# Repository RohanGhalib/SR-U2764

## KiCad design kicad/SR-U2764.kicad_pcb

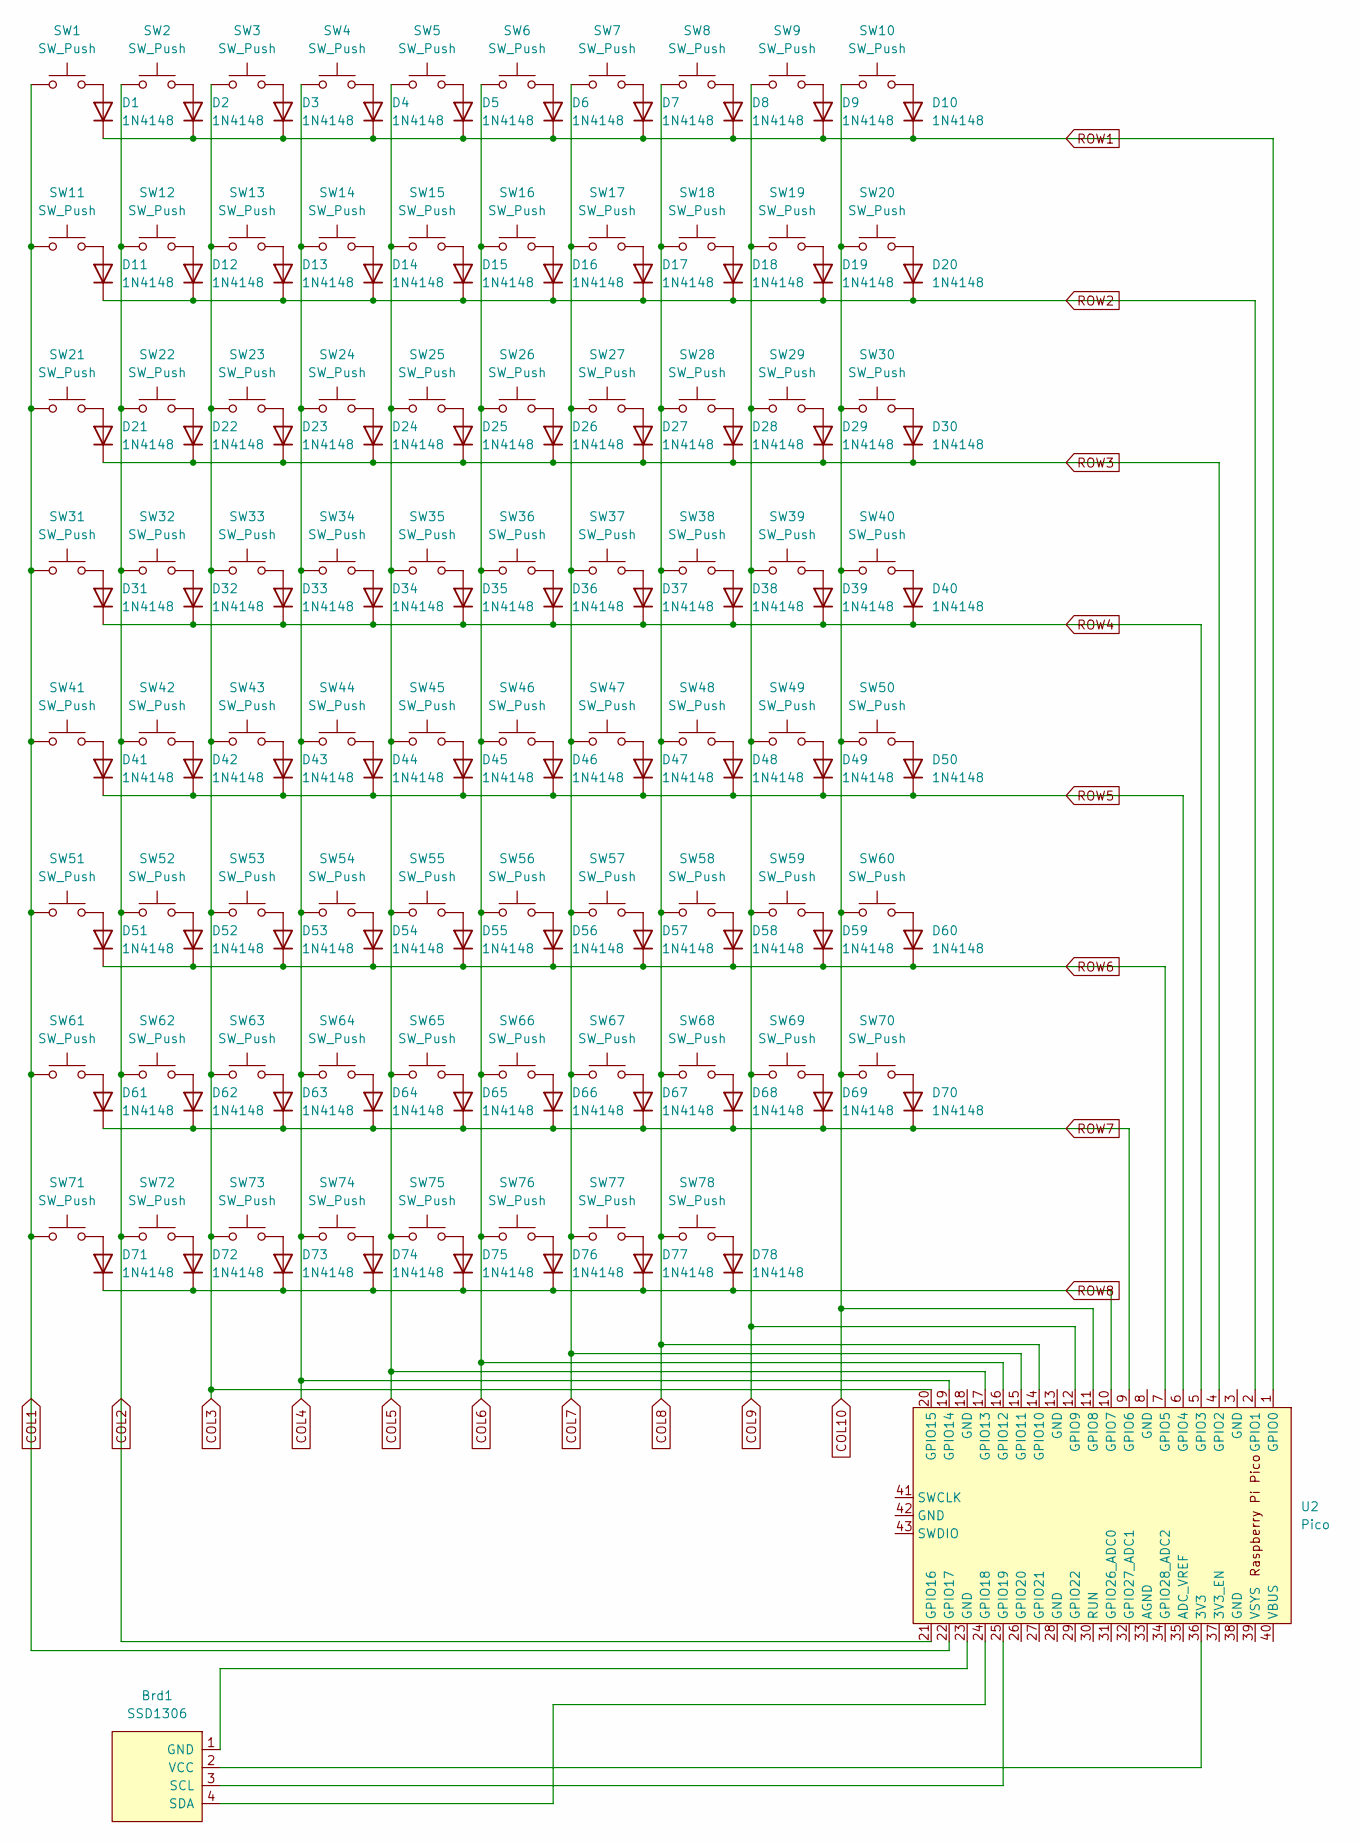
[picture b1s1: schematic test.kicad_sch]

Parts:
Brd1: SSD1306; Adafruit_SSD1306
D1, D2, D3, D4, D5, D6, D7, D8, D9, D10, D11, D12, D13, D14, D15, D16, D17, D18, D19, D20, D21, D22, D23, D24, D25, D26, D27, D28, D29, D30, D31, D32, D33, D34, D35, D36, D37, D38, D39, D40, D41, D42, D43, D44, D45, D46, D47, D48, D49, D50, D51, D52, D53, D54, D55, D56, D57, D58, D59, D60, D61, D62, D63, D64, D65, D66, D67, D68, D69, D70, D71, D72, D73, D74, D75, D76, D77, D78: 1N4148; D_DO-35_SOD27_P7.62mm_Horizontal
SW1, SW2, SW3, SW4, SW5, SW6, SW7, SW8, SW9, SW10, SW11, SW12, SW13, SW14, SW15, SW16, SW17, SW18, SW19, SW20, SW21, SW22, SW23, SW24, SW25, SW26, SW27, SW28, SW29, SW30, SW31, SW32, SW33, SW34, SW35, SW36, SW37, SW38, SW39, SW40, SW41, SW42, SW43, SW44, SW45, SW46, SW47, SW48, SW49, SW50, SW51, SW52, SW53, SW54, SW55, SW56, SW57, SW58, SW59, SW60, SW61, SW62, SW63, SW64, SW65, SW66, SW67, SW68, SW69, SW70, SW71, SW72, SW73, SW74, SW75, SW76, SW77, SW78: SW_Push; SW_Cherry_MX_1.00u_PCB
U2: Pico; RaspberryPi_Pico_Common_THT

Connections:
COL1: SW1.1, SW11.1, SW21.1, SW31.1, SW41.1, SW51.1, SW61.1, SW71.1, U2.22 (GPIO17)
COL2: SW2.1, SW12.1, SW22.1, SW32.1, SW42.1, SW52.1, SW62.1, SW72.1, U2.21 (GPIO16)
COL3: SW3.1, SW13.1, SW23.1, SW33.1, SW43.1, SW53.1, SW63.1, SW73.1, U2.20 (GPIO15)
COL4: SW4.1, SW14.1, SW24.1, SW34.1, SW44.1, SW54.1, SW64.1, SW74.1, U2.19 (GPIO14)
COL5: SW5.1, SW15.1, SW25.1, SW35.1, SW45.1, SW55.1, SW65.1, SW75.1, U2.17 (GPIO13)
COL6: SW6.1, SW16.1, SW26.1, SW36.1, SW46.1, SW56.1, SW66.1, SW76.1, U2.16 (GPIO12)
COL7: SW7.1, SW17.1, SW27.1, SW37.1, SW47.1, SW57.1, SW67.1, SW77.1, U2.15 (GPIO11)
COL8: SW8.1, SW18.1, SW28.1, SW38.1, SW48.1, SW58.1, SW68.1, SW78.1, U2.14 (GPIO10)
COL9: SW9.1, SW19.1, SW29.1, SW39.1, SW49.1, SW59.1, SW69.1, U2.12 (GPIO9)
COL10: SW10.1, SW20.1, SW30.1, SW40.1, SW50.1, SW60.1, SW70.1, U2.11 (GPIO8)
unnamed: Brd1.1 (GND), U2.23 (GND)
unnamed: Brd1.3 (SCL), U2.25 (GPIO19)
unnamed: Brd1.4 (SDA), U2.24 (GPIO18)
unnamed: Brd1.2 (VCC), U2.36 (3V3)
unnamed: D1.2 (A), SW1.2
unnamed: D2.2 (A), SW2.2
unnamed: D3.2 (A), SW3.2
unnamed: D4.2 (A), SW4.2
unnamed: D5.2 (A), SW5.2
unnamed: D6.2 (A), SW6.2
unnamed: D7.2 (A), SW7.2
unnamed: D8.2 (A), SW8.2
unnamed: D9.2 (A), SW9.2
unnamed: D10.2 (A), SW10.2
unnamed: D11.2 (A), SW11.2
unnamed: D12.2 (A), SW12.2
unnamed: D13.2 (A), SW13.2
unnamed: D14.2 (A), SW14.2
unnamed: D15.2 (A), SW15.2
unnamed: D16.2 (A), SW16.2
unnamed: D17.2 (A), SW17.2
unnamed: D18.2 (A), SW18.2
unnamed: D19.2 (A), SW19.2
unnamed: D20.2 (A), SW20.2
unnamed: D21.2 (A), SW21.2
unnamed: D22.2 (A), SW22.2
unnamed: D23.2 (A), SW23.2
unnamed: D24.2 (A), SW24.2
unnamed: D25.2 (A), SW25.2
unnamed: D26.2 (A), SW26.2
unnamed: D27.2 (A), SW27.2
unnamed: D28.2 (A), SW28.2
unnamed: D29.2 (A), SW29.2
unnamed: D30.2 (A), SW30.2
unnamed: D31.2 (A), SW31.2
unnamed: D32.2 (A), SW32.2
unnamed: D33.2 (A), SW33.2
unnamed: D34.2 (A), SW34.2
unnamed: D35.2 (A), SW35.2
unnamed: D36.2 (A), SW36.2
unnamed: D37.2 (A), SW37.2
unnamed: D38.2 (A), SW38.2
unnamed: D39.2 (A), SW39.2
unnamed: D40.2 (A), SW40.2
unnamed: D41.2 (A), SW41.2
unnamed: D42.2 (A), SW42.2
unnamed: D43.2 (A), SW43.2
unnamed: D44.2 (A), SW44.2
unnamed: D45.2 (A), SW45.2
unnamed: D46.2 (A), SW46.2
unnamed: D47.2 (A), SW47.2
unnamed: D48.2 (A), SW48.2
unnamed: D49.2 (A), SW49.2
unnamed: D50.2 (A), SW50.2
unnamed: D51.2 (A), SW51.2
unnamed: D52.2 (A), SW52.2
unnamed: D53.2 (A), SW53.2
unnamed: D54.2 (A), SW54.2
unnamed: D55.2 (A), SW55.2
unnamed: D56.2 (A), SW56.2
unnamed: D57.2 (A), SW57.2
unnamed: D58.2 (A), SW58.2
unnamed: D59.2 (A), SW59.2
unnamed: D60.2 (A), SW60.2
unnamed: D61.2 (A), SW61.2
unnamed: D62.2 (A), SW62.2
unnamed: D63.2 (A), SW63.2
unnamed: D64.2 (A), SW64.2
unnamed: D65.2 (A), SW65.2
unnamed: D66.2 (A), SW66.2
unnamed: D67.2 (A), SW67.2
unnamed: D68.2 (A), SW68.2
unnamed: D69.2 (A), SW69.2
unnamed: D70.2 (A), SW70.2
unnamed: D71.2 (A), SW71.2
unnamed: D72.2 (A), SW72.2
unnamed: D73.2 (A), SW73.2
unnamed: D74.2 (A), SW74.2
unnamed: D75.2 (A), SW75.2
unnamed: D76.2 (A), SW76.2
unnamed: D77.2 (A), SW77.2
unnamed: D78.2 (A), SW78.2
ROW1: D1.1 (K), D2.1 (K), D3.1 (K), D4.1 (K), D5.1 (K), D6.1 (K), D7.1 (K), D8.1 (K), D9.1 (K), D10.1 (K), U2.1 (GPIO0)
ROW2: D11.1 (K), D12.1 (K), D13.1 (K), D14.1 (K), D15.1 (K), D16.1 (K), D17.1 (K), D18.1 (K), D19.1 (K), D20.1 (K), U2.2 (GPIO1)
ROW3: D21.1 (K), D22.1 (K), D23.1 (K), D24.1 (K), D25.1 (K), D26.1 (K), D27.1 (K), D28.1 (K), D29.1 (K), D30.1 (K), U2.4 (GPIO2)
ROW4: D31.1 (K), D32.1 (K), D33.1 (K), D34.1 (K), D35.1 (K), D36.1 (K), D37.1 (K), D38.1 (K), D39.1 (K), D40.1 (K), U2.5 (GPIO3)
ROW5: D41.1 (K), D42.1 (K), D43.1 (K), D44.1 (K), D45.1 (K), D46.1 (K), D47.1 (K), D48.1 (K), D49.1 (K), D50.1 (K), U2.6 (GPIO4)
ROW6: D51.1 (K), D52.1 (K), D53.1 (K), D54.1 (K), D55.1 (K), D56.1 (K), D57.1 (K), D58.1 (K), D59.1 (K), D60.1 (K), U2.7 (GPIO5)
ROW7: D61.1 (K), D62.1 (K), D63.1 (K), D64.1 (K), D65.1 (K), D66.1 (K), D67.1 (K), D68.1 (K), D69.1 (K), D70.1 (K), U2.9 (GPIO6)
ROW8: D71.1 (K), D72.1 (K), D73.1 (K), D74.1 (K), D75.1 (K), D76.1 (K), D77.1 (K), D78.1 (K), U2.10 (GPIO7)

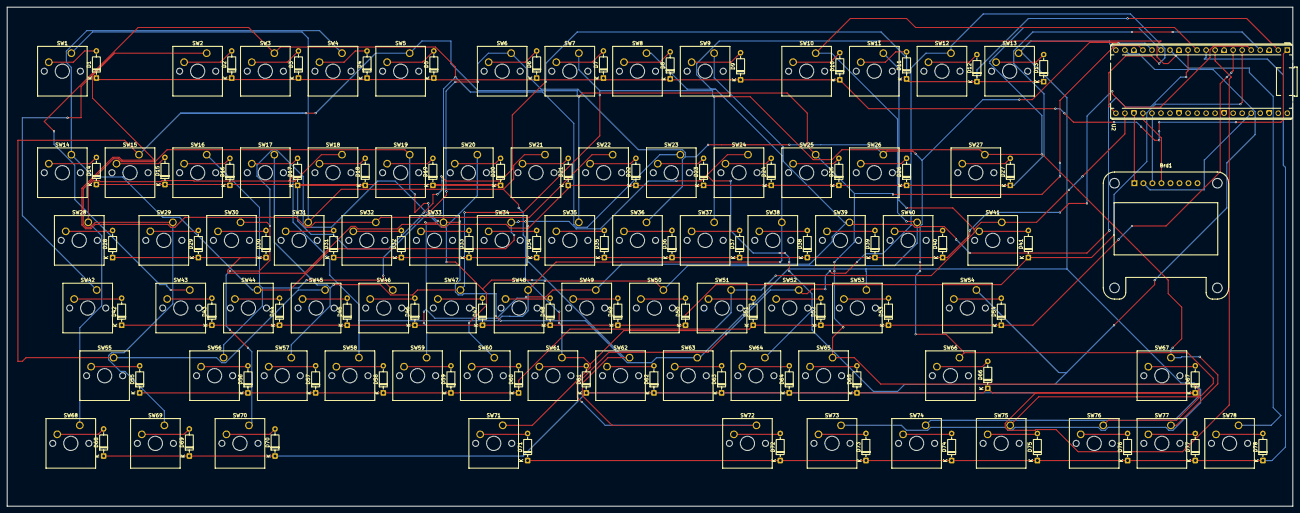
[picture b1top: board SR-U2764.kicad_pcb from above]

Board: 2 copper layers, 361.9 x 140.5 mm, 158 parts (0 on the bottom side), 100 nets.

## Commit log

2025-07-11 update journal
2025-07-12 Added the first drafts schematic, and pcb
2025-07-16 update pcb and update journal
